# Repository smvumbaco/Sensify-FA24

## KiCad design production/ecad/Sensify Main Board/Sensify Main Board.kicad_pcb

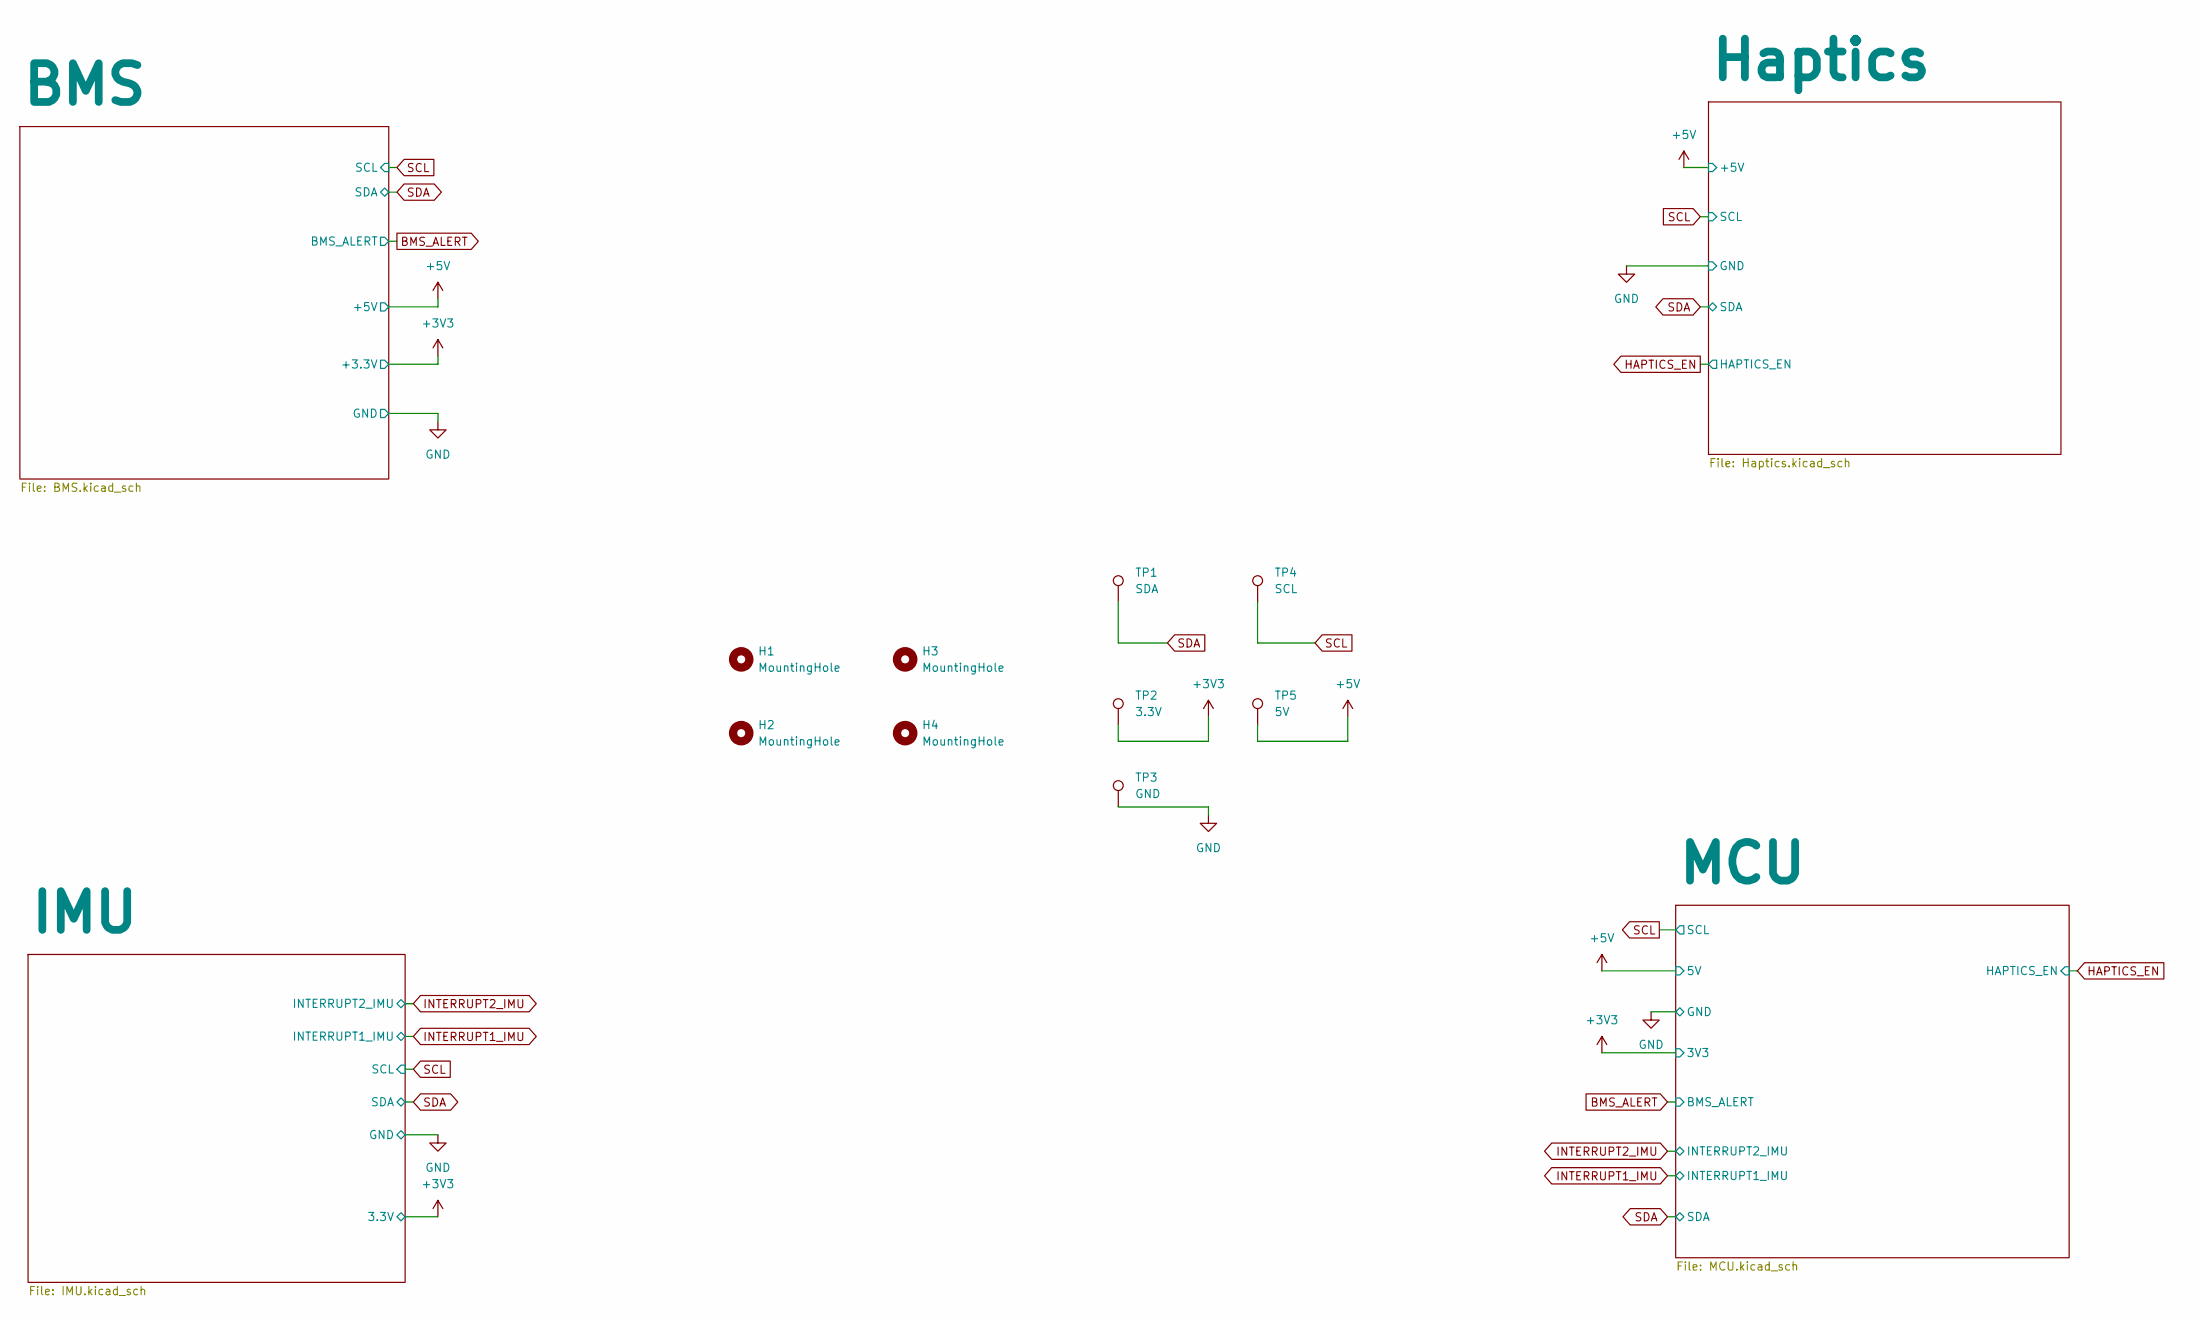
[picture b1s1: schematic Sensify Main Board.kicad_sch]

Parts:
H1, H2, H3, H4: MountingHole; MountingHole_3.2mm_M3
TP1: SDA; TestPoint_Pad_D2.0mm
TP2: 3.3V; TestPoint_Pad_D2.0mm
TP3: GND; TestPoint_Pad_D2.0mm
TP4: SCL; TestPoint_Pad_D2.0mm
TP5: 5V; TestPoint_Pad_D2.0mm

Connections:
+3V3: TP2.1; also elsewhere on the board
+5V: TP5.1; also elsewhere on the board
GND: TP3.1; also elsewhere on the board
SCL: TP4.1; also elsewhere on the board
SDA: TP1.1; also elsewhere on the board

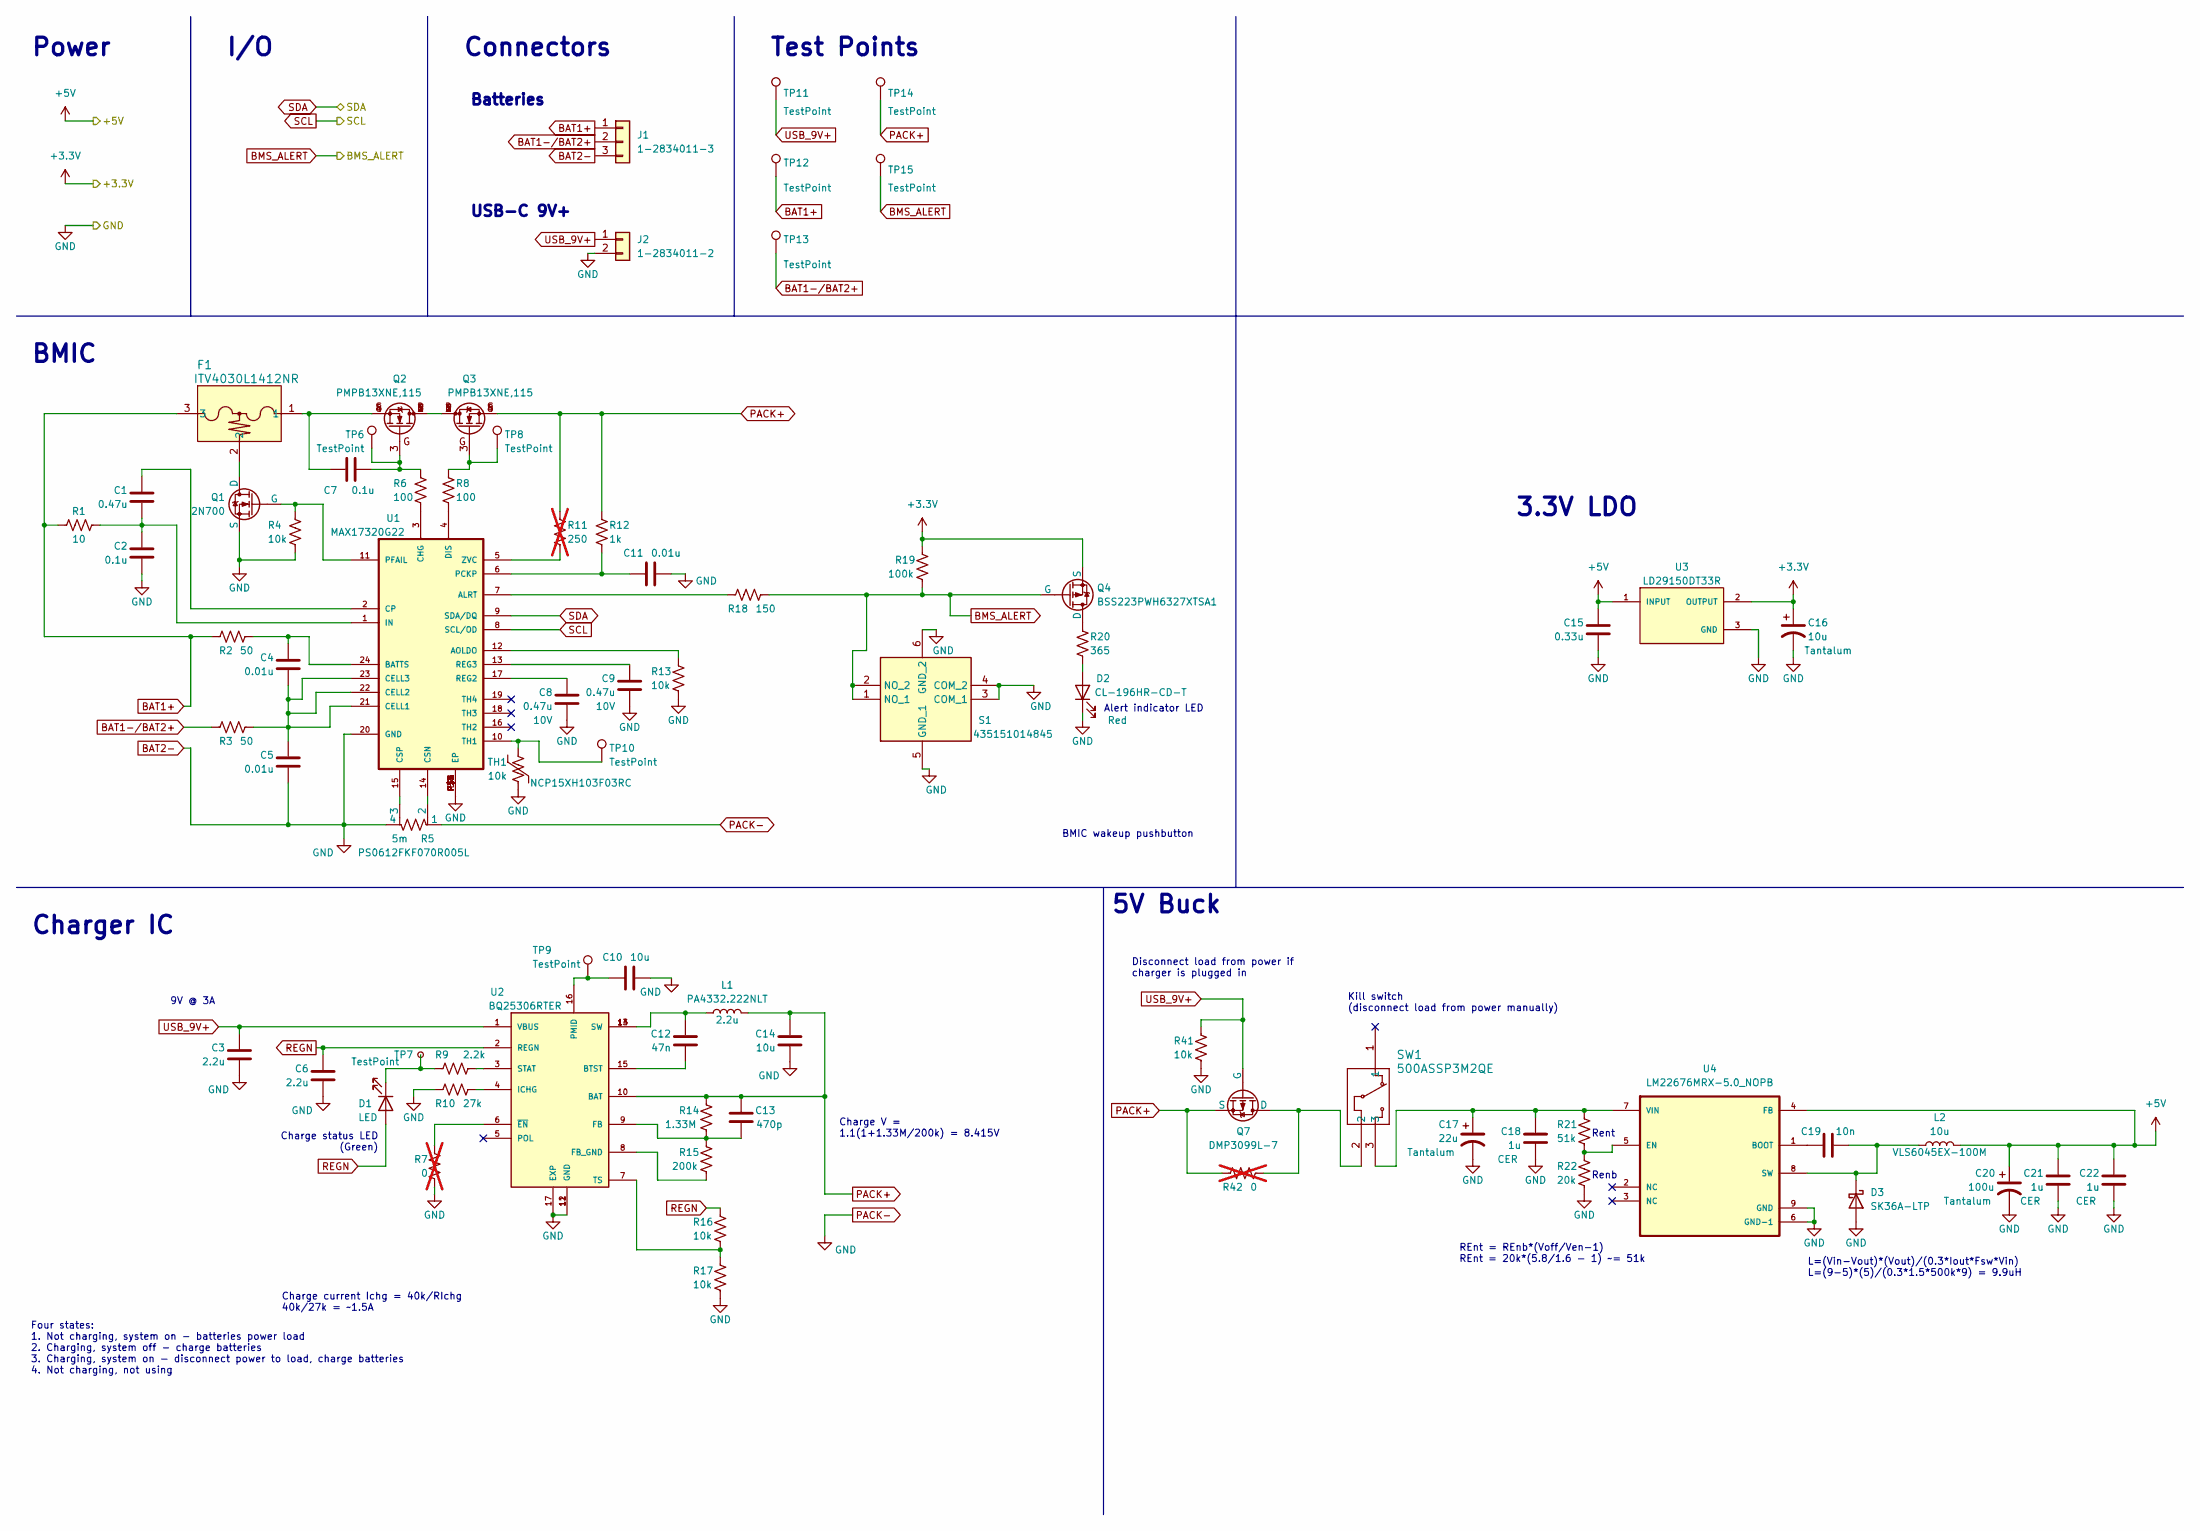
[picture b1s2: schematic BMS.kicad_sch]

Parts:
C1: 0.47u; C_0402_1005Metric_Pad0.74x0.62mm_HandSolder; LCSC C92361
C2, C7: 0.1u; C_0402_1005Metric_Pad0.74x0.62mm_HandSolder; LCSC C1581
C3: 2.2u; C_0603_1608Metric_Pad1.08x0.95mm_HandSolder; LCSC C43922
C4, C5, C11: 0.01u; C_0402_1005Metric_Pad0.74x0.62mm_HandSolder; LCSC C1524
C6: 2.2u; C_0402_1005Metric_Pad0.74x0.62mm_HandSolder; LCSC C72203
C8, C9: 0.47u; C_0402_1005Metric_Pad0.74x0.62mm_HandSolder; Voltage 10V; LCSC C92361
C10, C14: 10u; C_0805_2012Metric_Pad1.18x1.45mm_HandSolder; LCSC C15850
C12: 47n; C_0402_1005Metric_Pad0.74x0.62mm_HandSolder; LCSC C82219
C13: 470p; C_0402_1005Metric_Pad0.74x0.62mm_HandSolder; LCSC C26412
C15: 0.33u; C_0603_1608Metric_Pad1.08x0.95mm_HandSolder; Voltage 10V; LCSC C14790
C16: 10u; T491A; Part number T491A106K010AT; LCSC C15850
C17: 22u; CAPPM3528X210N; LCSC C110037
C18, C21, C22: 1u; C_0603_1608Metric_Pad1.08x0.95mm_HandSolder; LCSC C15849
C19: 10n; C_0603_1608Metric_Pad1.08x0.95mm_HandSolder; LCSC C7248
C20: 100u; CAPPM3528X210N; LCSC C1953001
D1: LED; D_0603_1608Metric_Pad1.05x0.95mm_HandSolder; Part number LTST-C190GKT; LCSC C125093
D2: CL-196HR-CD-T; D_0603_1608Metric_Pad1.05x0.95mm_HandSolder; LCSC C6150013
D3: SK36A-LTP; DIOM5225X244N; LCSC C106867
F1: ITV4030L1412NR; ITV4030_LTF; LCSC C3672263
J1: 1-2834011-3; 128340113
J2: 1-2834011-2; 128340112
L1: 2.2u; IND_PA4332.222NLT_PUL; part number PA4332.222NLT; LCSC C3222957
L2: 10u; IND_VLS6045EX-100M; part number VLS6045EX-100M; LCSC C360734
Q1: 2N700; SOT95P240X111-3N; LCSC C8545
Q2, Q3: PMPB13XNE,115; DFN2020MD-6_SOT1220_NEX; LCSC C553019
Q4: BSS223PWH6327XTSA1; SOT65P210X100-3N; LCSC C3278612
Q7: DMP3099L-7; DMP3099L-7_DIO; LCSC C155244
R1: 10; R_0805_2012Metric_Pad1.20x1.40mm_HandSolder; LCSC C103908
R2, R3: 50; R_0805_2012Metric_Pad1.20x1.40mm_HandSolder; LCSC C2828807
R4, R13, R16, R17: 10k; R_0402_1005Metric_Pad0.72x0.64mm_HandSolder; LCSC C881209
R5: 5m; PS0612_2-10mOHM_YAG; Part number PS0612FKF070R005L
R6, R8: 100; R_0402_1005Metric_Pad0.72x0.64mm_HandSolder; LCSC C102747
R7, R42: 0; R_0402_1005Metric_Pad0.72x0.64mm_HandSolder; LCSC C60485; not fitted
R9: 2.2k; R_0402_1005Metric_Pad0.72x0.64mm_HandSolder; LCSC C25933
R10: 27k; R_0402_1005Metric_Pad0.72x0.64mm_HandSolder; Part number ERA-2ARB273X; LCSC C11896
R11: 250; R_0402_1005Metric_Pad0.72x0.64mm_HandSolder; LCSC C114755; not fitted
R12: 1k; R_0402_1005Metric_Pad0.72x0.64mm_HandSolder; LCSC C226698
R14: 1.33M; R_0402_1005Metric_Pad0.72x0.64mm_HandSolder; LCSC C5713265
R15: 200k; R_0402_1005Metric_Pad0.72x0.64mm_HandSolder; LCSC C25764
R18: 150; R_0402_1005Metric_Pad0.72x0.64mm_HandSolder; LCSC C25143
R19: 100k; R_0402_1005Metric_Pad0.72x0.64mm_HandSolder; LCSC C102750
R20: 365; R_0402_1005Metric_Pad0.72x0.64mm_HandSolder; LCSC C227016
R21: 51k; R_0603_1608Metric_Pad0.98x0.95mm_HandSolder; LCSC C95329
R22: 20k; R_0603_1608Metric_Pad0.98x0.95mm_HandSolder; LCSC C125934
R41: 10k; R_0402_1005Metric; LCSC C881209
S1: 435151014845; Manufacturer_Part_Number 435151014845; Mouser Part Number 710-435151014845
SW1: 500ASSP3M2QE; 500ASSP3M2QE_EWI
TH1: 10k; R_0402_1005Metric_Pad0.72x0.64mm_HandSolder; Part number NCP15XH103F03RC; LCSC C77131
TP6, TP7, TP8, TP9, TP10, TP11, TP12, TP13, TP14, TP15: TestPoint; TestPoint_Pad_D1.5mm
U1: MAX17320G22; TQFN-24; LCSC C2914309
U2: BQ25306RTER; IC_BQ25306RTER; PARTREV A; LCSC C3682611
U3: LD29150DT33R; DPAK456P972X240-3N; PARTREV 20; LCSC C155674
U4: LM22676MRX-5.0_NOPB; VREG_LM5017MR_NOPB; LCSC C485622

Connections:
+3V3: C16.1, Q4.3 (S), R19.1, U3.2 (OUTPUT); also elsewhere on the board
+5V: C15.1, C20.1, C21.1, C22.1, L2.2, U3.1 (INPUT), U4.4 (FB); also elsewhere on the board
BAT1+: F1.3, J1.1, R1.1, R2.2, TP12.1
BAT1-/BAT2+: J1.2, R3.2, TP13.1
BMS_ALERT: Q4.2 (G), R18.1, R19.2, S1.1 (NO_1), S1.2 (NO_2), TP15.1; also elsewhere on the board
GND: C2.2, C3.2, C5.2, C6.2, C8.2, C9.2, C10.2, C11.2, C14.2, C15.2, C16.2, C17.2, C18.2, C20.2, C21.2, C22.2, D2.1 (K), D3.2, J1.3, J2.2, Q1.3 (S), R4.2, R5.1, R5.4, R7.2, R10.2, R13.2, R17.2, R22.2, R41.2, S1.3 (COM_1), S1.4 (COM_2), S1.5 (GND_1), S1.6 (GND_2), TH1.1, U1.20 (GND), U1.EP, U1.P$1 (EP), U1.P$2 (EP), U1.P$3 (EP), U1.P$4 (EP), U1.P$5 (EP), U2.11 (GND), U2.12 (GND), U2.17 (EXP), U3.3 (GND), U4.6 (GND-1), U4.9 (GND); also elsewhere on the board
unnamed: C7.1, F1.1, Q2.4 (S), Q2.8 (S)
unnamed: C12.1, L1.1, U2.13 (SW), U2.14 (SW)
unnamed: D1.1 (K), R9.2, TP7.1
unnamed: D2.2 (A), R20.2
unnamed: F1.2, Q1.1 (D)
unnamed: Q1.2 (G), R4.1, U1.11 (PFAIL)
unnamed: Q2.1 (D), Q2.2 (D), Q2.5 (D), Q2.6 (D), Q2.7 (D), Q3.1 (D), Q3.2 (D), Q3.5 (D), Q3.6 (D), Q3.7 (D)
unnamed: C7.2, Q2.3 (G), R6.1, TP6.1
unnamed: Q3.3 (G), R8.1, TP8.1
unnamed: Q4.1 (D), R20.1
unnamed: Q7.1 (D), R42.1, SW1.2
unnamed: R18.2, U1.7 (ALRT)
unnamed: R13.1, U1.12 (AOLDO)
unnamed: C4.1, R2.1, U1.24 (BATTS)
unnamed: C4.2, C5.1, R3.1, U1.21 (CELL1), U1.22 (CELL2), U1.23 (CELL3)
unnamed: R6.2, U1.3 (CHG)
unnamed: C1.1, U1.2 (CP)
unnamed: R5.2, U1.14 (CSN)
unnamed: R5.3, U1.15 (CSP)
unnamed: R8.2, U1.4 (DIS)
unnamed: C1.2, C2.1, R1.2, U1.1 (IN)
unnamed: C11.1, R12.2, U1.6 (PCKP)
unnamed: C8.1, U1.17 (REG2)
unnamed: C9.1, U1.13 (REG3)
unnamed: TH1.2, TP10.1, U1.10 (TH1)
unnamed: R11.2, U1.5 (ZVC)
unnamed: C12.2, U2.15 (BTST)
unnamed: C13.2, R14.2, R15.1, U2.9 (FB)
unnamed: R15.2, U2.8 (FB_GND)
unnamed: R10.1, U2.4 (ICHG)
unnamed: C10.1, TP9.1, U2.16 (PMID)
unnamed: R9.1, U2.3 (STAT)
unnamed: R16.2, R17.1, U2.7 (TS)
unnamed: R7.1, U2.6 (~EN)
unnamed: C19.1, U4.1 (BOOT)
unnamed: R21.2, R22.1, U4.5 (EN)
unnamed: C19.2, D3.1, L2.1, U4.8 (SW)
unnamed: C17.1, C18.1, R21.1, SW1.3, U4.7 (VIN)
PACK+: C13.1, C14.1, L1.2, Q3.4 (S), Q3.8 (S), Q7.3 (S), R11.1, R12.1, R14.1, R42.2, TP14.1, U2.10 (BAT)
REGN: C6.1, D1.2 (A), R16.1, U2.2 (REGN)
SCL: U1.8 (SCL/OD); also elsewhere on the board
SDA: U1.9 (SDA/DQ); also elsewhere on the board
USB_9V+: C3.1, J2.1, Q7.2 (G), R41.1, TP11.1, U2.1 (VBUS)

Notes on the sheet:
REnt = REnb*(Voff/Ven-1) REnt = 20k*(5.8/1.6 - 1) ~= 51k
USB-C 9V+
Rent
5V Buck
BMIC wakeup pushbutton
Test Points
I/O
Alert indicator LED
Connectors
Charge V = 1.1(1+1.33M/200k) = 8.415V
L=(Vin-Vout)*(Vout)/(0.3*Iout*Fsw*Vin) L=(9-5)*(5)/(0.3*1.5*500k*9) = 9.9uH
3.3V LDO
Charger IC
Kill switch (disconnect load from power manually)
Batteries
Four states: 1. Not charging, system on - batteries power load 2. Charging, system off - charge batteries 3. Charging, system on - disconnect power to load, charge batteries 4. Not charging, not using
BMIC
Disconnect load from power if charger is plugged in
9V @ 3A
Power
Charge current Ichg = 40k/RIchg 40k/27k = ~1.5A
Charge status LED (Green)
Renb

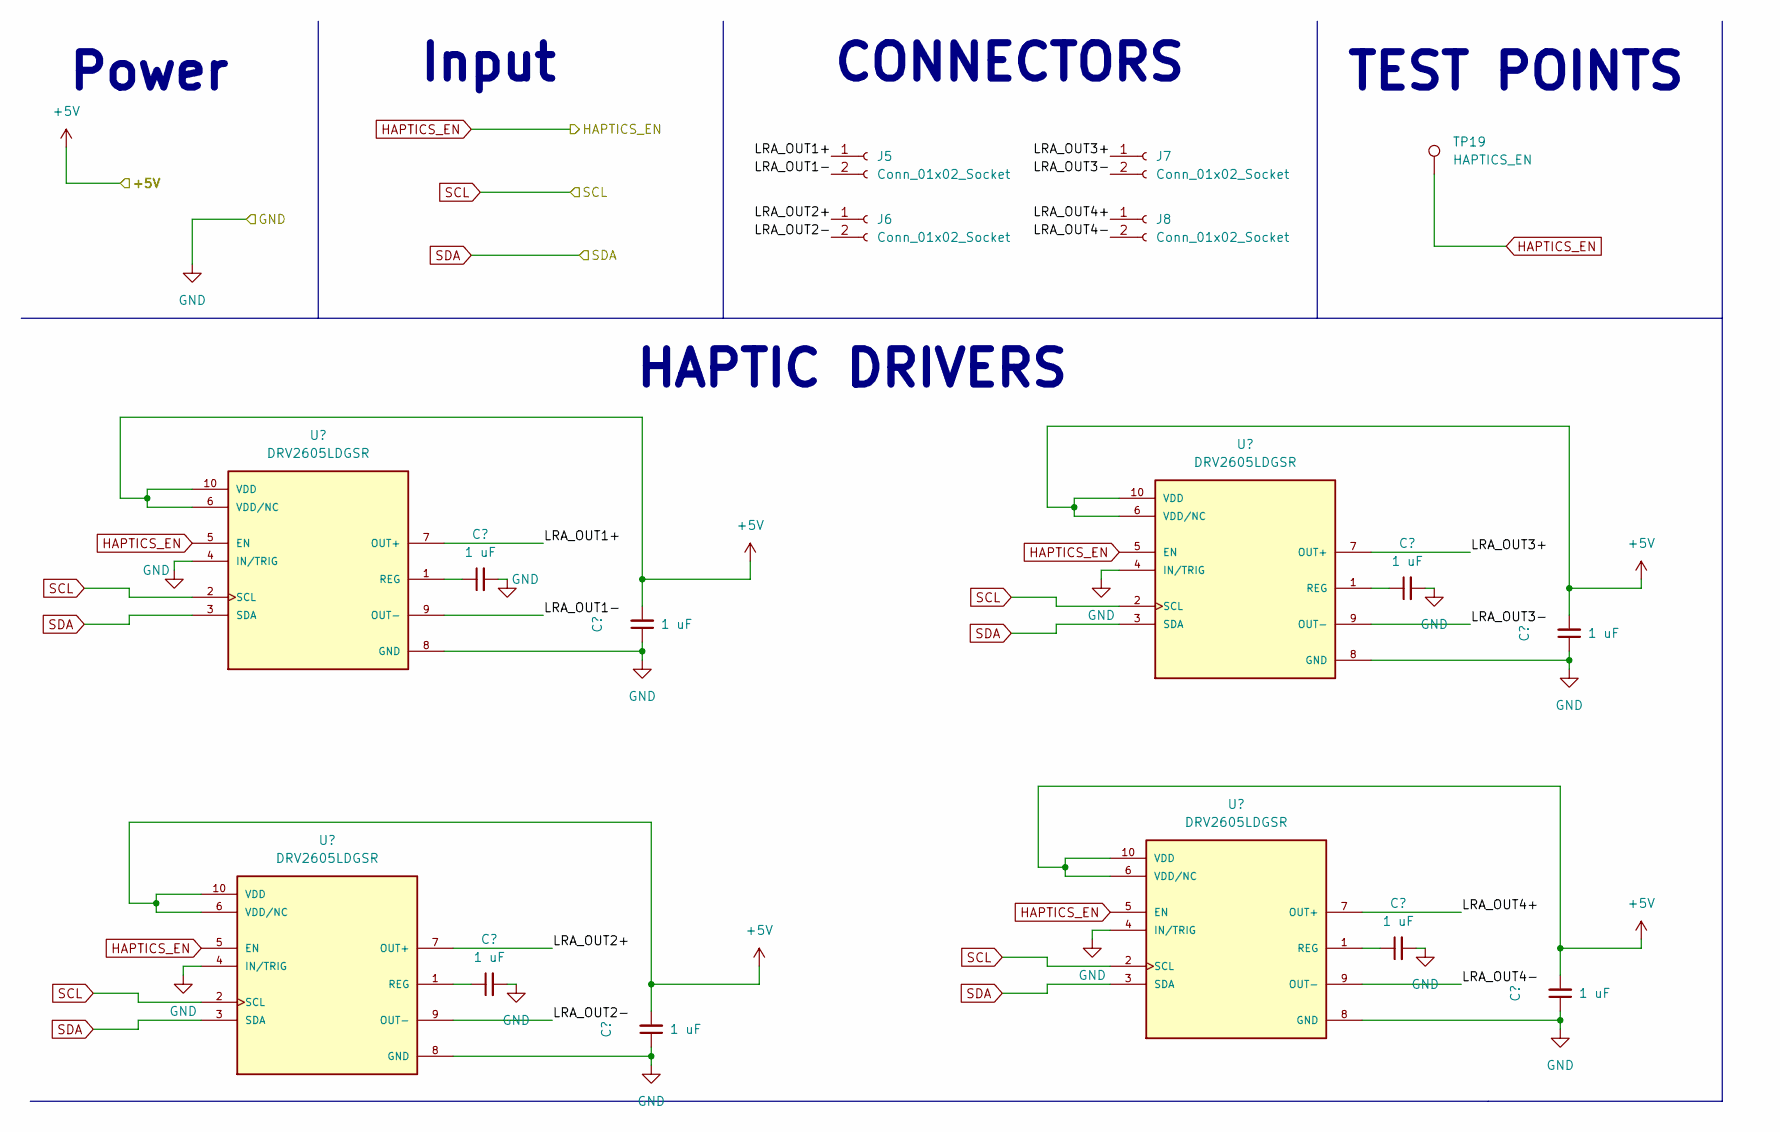
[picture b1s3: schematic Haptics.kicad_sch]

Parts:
C29, C30, C31, C32, C33, C34, C35, C36: 1 uF; C_0402_1005Metric; LCSC C87144
J5, J6, J7, J8: Conn_01x02_Socket; JST_EH_B2B-EH-A_1x02_P2.50mm_Vertical
TP19: HAPTICS_EN; TestPoint_Pad_D2.0mm
U7, U8, U9, U10: DRV2605LDGSR; SOP50P490X110-10N; PARTREV D; LCSC C527464

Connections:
+5V: C31.2, C32.2, C35.2, C36.2, U7.6 (VDD/NC), U7.10 (VDD), U8.6 (VDD/NC), U8.10 (VDD), U9.6 (VDD/NC), U9.10 (VDD), U10.6 (VDD/NC), U10.10 (VDD); also elsewhere on the board
/Haptics/LRA_OUT1+: J5.1, U7.7 (OUT+)
/Haptics/LRA_OUT1-: J5.2, U7.9 (OUT-)
/Haptics/LRA_OUT2+: J6.1, U8.7 (OUT+)
/Haptics/LRA_OUT2-: J6.2, U8.9 (OUT-)
/Haptics/LRA_OUT3+: J7.1, U10.7 (OUT+)
/Haptics/LRA_OUT3-: J7.2, U10.9 (OUT-)
/Haptics/LRA_OUT4+: J8.1, U9.7 (OUT+)
/Haptics/LRA_OUT4-: J8.2, U9.9 (OUT-)
GND: C29.2, C30.2, C31.1, C32.1, C33.2, C34.2, C35.1, C36.1, U7.4 (IN/TRIG), U7.8 (GND), U8.4 (IN/TRIG), U8.8 (GND), U9.4 (IN/TRIG), U9.8 (GND), U10.4 (IN/TRIG), U10.8 (GND); also elsewhere on the board
HAPTICS_EN: TP19.1, U7.5 (EN), U8.5 (EN), U9.5 (EN), U10.5 (EN); also elsewhere on the board
unnamed: C29.1, U7.1 (REG)
unnamed: C30.1, U8.1 (REG)
unnamed: C33.1, U9.1 (REG)
unnamed: C34.1, U10.1 (REG)
SCL: U7.2 (SCL), U8.2 (SCL), U9.2 (SCL), U10.2 (SCL); also elsewhere on the board
SDA: U7.3 (SDA), U8.3 (SDA), U9.3 (SDA), U10.3 (SDA); also elsewhere on the board

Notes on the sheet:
HAPTIC DRIVERS
CONNECTORS
Input
TEST POINTS
Power

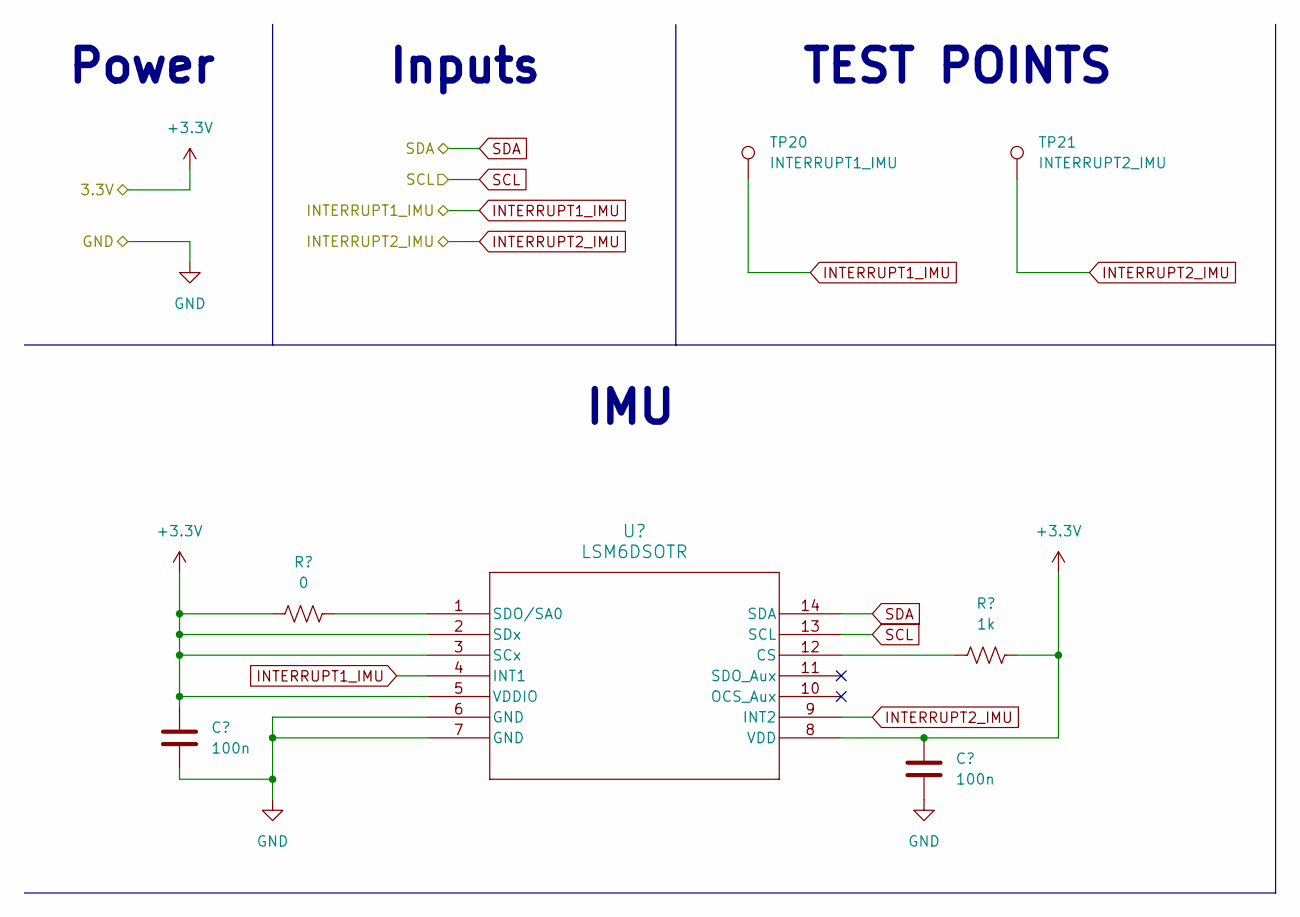
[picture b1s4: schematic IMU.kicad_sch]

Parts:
C37, C38: 100n; C_0402_1005Metric; LCSC C2180807
R39: 0; R_0402_1005Metric; LCSC C60485
R40: 1k; R_0402_1005Metric; LCSC C226698
TP20: INTERRUPT1_IMU; TestPoint_Pad_D2.0mm
TP21: INTERRUPT2_IMU; TestPoint_Pad_D2.0mm
U11: LSM6DSOTR; IMU_LSM6DSOTR; LCSC C2655100

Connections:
+3V3: C37.1, C38.1, R39.1, R40.2, U11.2 (SDx), U11.3 (SCx), U11.5 (VDDIO), U11.8 (VDD); also elsewhere on the board
GND: C37.2, C38.2, U11.6 (GND), U11.7 (GND); also elsewhere on the board
INTERRUPT1_IMU: TP20.1, U11.4 (INT1); also elsewhere on the board
INTERRUPT2_IMU: TP21.1, U11.9 (INT2); also elsewhere on the board
unnamed: R40.1, U11.12 (CS)
unnamed: R39.2, U11.1 (SDO/SA0)
SCL: U11.13 (SCL); also elsewhere on the board
SDA: U11.14 (SDA); also elsewhere on the board

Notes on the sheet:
IMU
Inputs
TEST POINTS
Power

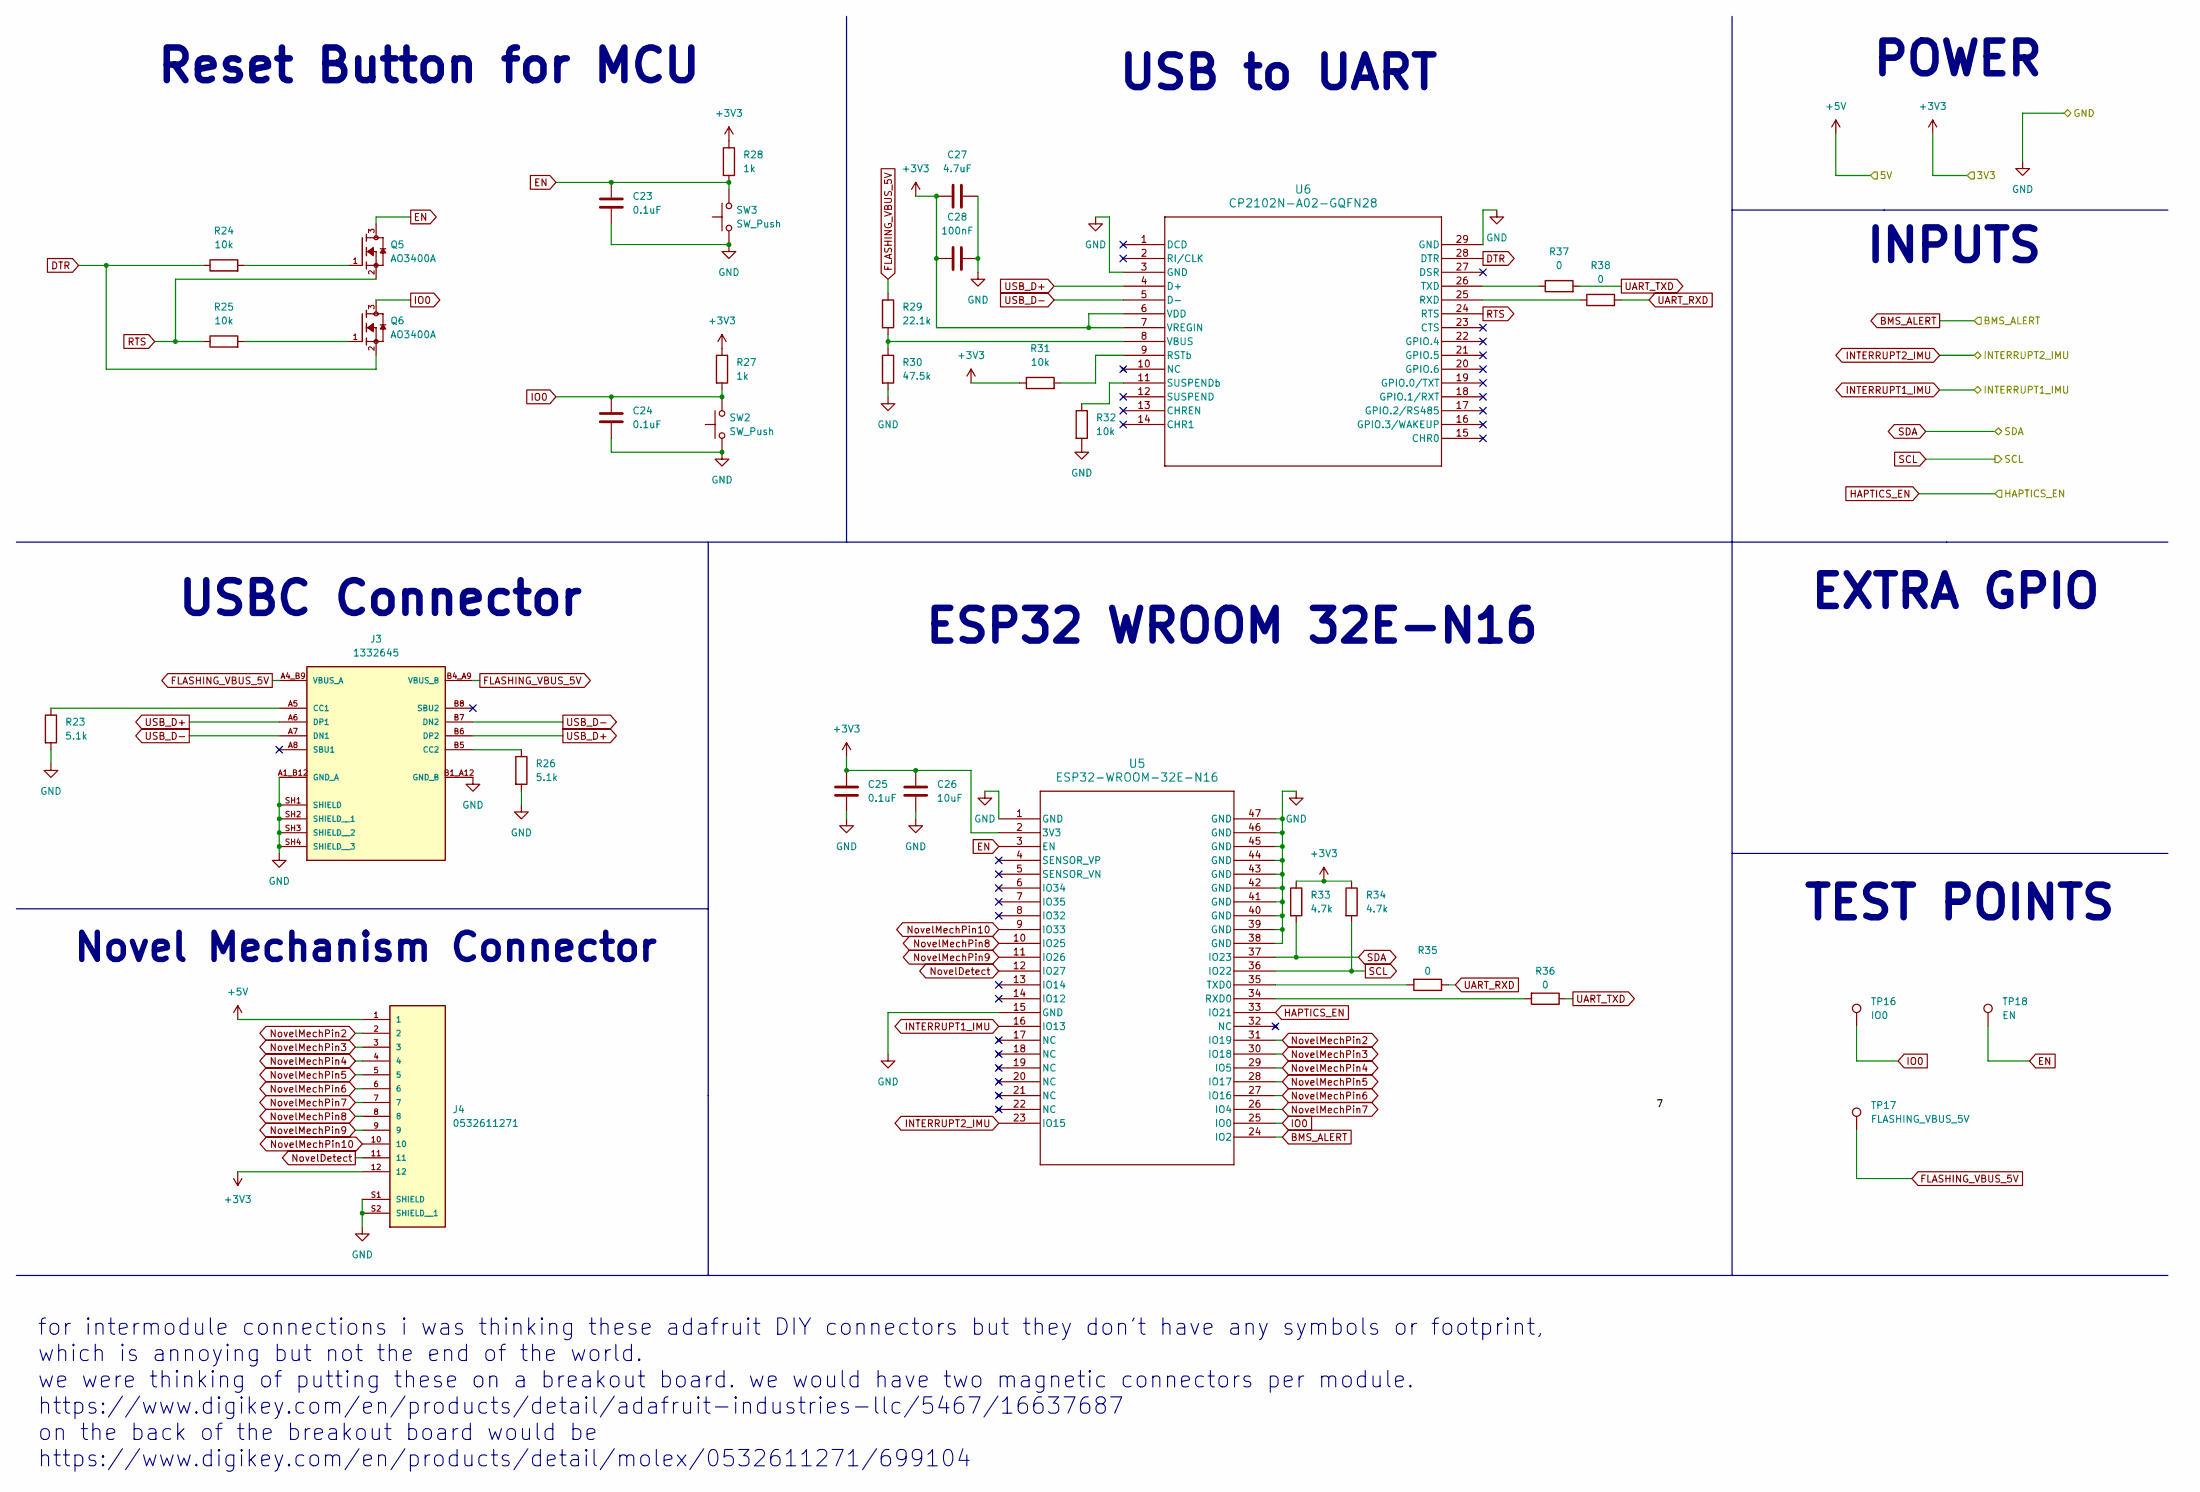
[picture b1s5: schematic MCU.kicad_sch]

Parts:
C23, C24, C25: 0.1uF; C_0402_1005Metric; LCSC C2180807
C26: 10uF; C_0402_1005Metric; LCSC C412251
C27: 4.7uF; C_0402_1005Metric; LCSC C5718966
C28: 100nF; C_0402_1005Metric; LCSC C2180807
J3: 1332645; PHOENIX_1332645; PARTREV 17.01.2022; LCSC C19193265
J4: 0532611271; MOLEX_0532611271; PARTREV J; LCSC C17393781
Q5, Q6: AO3400A; SOT95P280X125-3N; PARTREV L; LCSC C20917
R23, R26: 5.1k; R_0402_1005Metric; LCSC C105872
R24, R25, R31, R32: 10k; R_0402_1005Metric; LCSC C881209
R27, R28: 1k; R_0402_1005Metric; LCSC C226698
R29: 22.1k; R_0402_1005Metric; LCSC C163478
R30: 47.5k; R_0402_1005Metric; LCSC C137974
R33, R34: 4.7k; R_0402_1005Metric; LCSC C105870
R35, R36, R37, R38: 0; R_0402_1005Metric; LCSC C60485
SW2, SW3: SW_Push; SW_1825910-6-4
TP16: IO0; TestPoint_Pad_D2.0mm
TP17: FLASHING_VBUS_5V; TestPoint_Pad_D2.0mm
TP18: EN; TestPoint_Pad_D2.0mm
U5: ESP32-WROOM-32E-N16; ESP32-WROOM-32E_EXP; LCSC C701343
U6: CP2102N-A02-GQFN28; QFN28_5X5_SIL-M; LCSC C1550553

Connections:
+3V3: C25.1, C26.1, C27.1, C28.1, J4.12, R27.1, R28.1, R31.1, R33.1, R34.1, U5.2 (3V3), U6.6 (VDD), U6.7 (VREGIN); also elsewhere on the board
+5V: J4.1; also elsewhere on the board
BMS_ALERT: U5.24 (IO2); also elsewhere on the board
DTR: Q6.2, R24.1, U6.28 (DTR)
EN: C23.1, Q5.3, R28.2, SW3.2, TP18.1, U5.3 (EN)
FLASHING_VBUS_5V: J3.A4_B9 (VBUS_A), J3.B4_A9 (VBUS_B), R29.1, TP17.1
GND: C23.2, C24.2, C25.2, C26.2, C27.2, C28.2, J3.A1_B12 (GND_A), J3.B1_A12 (GND_B), J3.SH1 (SHIELD), J3.SH2 (SHIELD__1), J3.SH3 (SHIELD__2), J3.SH4 (SHIELD__3), J4.S1 (SHIELD), J4.S2 (SHIELD__1), R23.2, R26.2, R30.2, R32.2, SW2.1, SW3.1, U5.1 (GND), U5.15 (GND), U5.38 (GND), U5.39 (GND), U5.40 (GND), U5.41 (GND), U5.42 (GND), U5.43 (GND), U5.44 (GND), U5.45 (GND), U5.46 (GND), U5.47 (GND), U6.3 (GND), U6.29 (GND); also elsewhere on the board
HAPTICS_EN: U5.33 (IO21); also elsewhere on the board
INTERRUPT1_IMU: U5.16 (IO13); also elsewhere on the board
INTERRUPT2_IMU: U5.23 (IO15); also elsewhere on the board
IO0: C24.1, Q6.3, R27.2, SW2.2, TP16.1, U5.25 (IO0)
unnamed: J3.A5 (CC1), R23.1
unnamed: J3.B5 (CC2), R26.1
unnamed: Q5.1, R24.2
unnamed: Q6.1, R25.2
unnamed: R36.2, U5.34 (RXD0)
unnamed: R35.2, U5.35 (TXD0)
unnamed: R31.2, U6.9 (RSTb)
unnamed: R38.1, U6.25 (RXD)
unnamed: R32.1, U6.11 (SUSPENDb)
unnamed: R37.1, U6.26 (TXD)
unnamed: R29.2, R30.1, U6.8 (VBUS)
NovelDetect: J4.11, U5.12 (IO27)
NovelMechPin2: J4.2, U5.31 (IO19)
NovelMechPin3: J4.3, U5.30 (IO18)
NovelMechPin4: J4.4, U5.29 (IO5)
NovelMechPin5: J4.5, U5.28 (IO17)
NovelMechPin6: J4.6, U5.27 (IO16)
NovelMechPin7: J4.7, U5.26 (IO4)
NovelMechPin8: J4.8, U5.10 (IO25)
NovelMechPin9: J4.9, U5.11 (IO26)
NovelMechPin10: J4.10, U5.9 (IO33)
RTS: Q5.2, R25.1, U6.24 (RTS)
SCL: R34.2, U5.36 (IO22); also elsewhere on the board
SDA: R33.2, U5.37 (IO23); also elsewhere on the board
UART_RXD: R35.1, R38.2
UART_TXD: R36.1, R37.2
USB_D+: J3.A6 (DP1), J3.B6 (DP2), U6.4 (D+)
USB_D-: J3.A7 (DN1), J3.B7 (DN2), U6.5 (D-)

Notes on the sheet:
Novel Mechanism Connector
POWER
USBC Connector
ESP32 WROOM 32E-N16
for intermodule connections i was thinking these adafruit DIY connectors but they don't have any symbols or footprint, which is annoying but not the end of the world. we were thinking of putting these on a breakout board. we would have two magnetic connectors per module. https://www.digikey.com/en/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
Reset Button for MCU
EXTRA GPIO
USB to UART
INPUTS
TEST POINTS

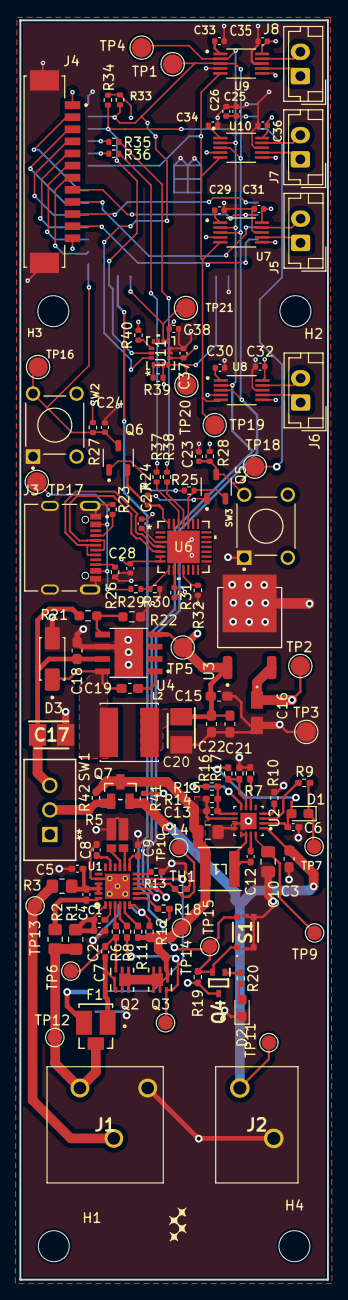
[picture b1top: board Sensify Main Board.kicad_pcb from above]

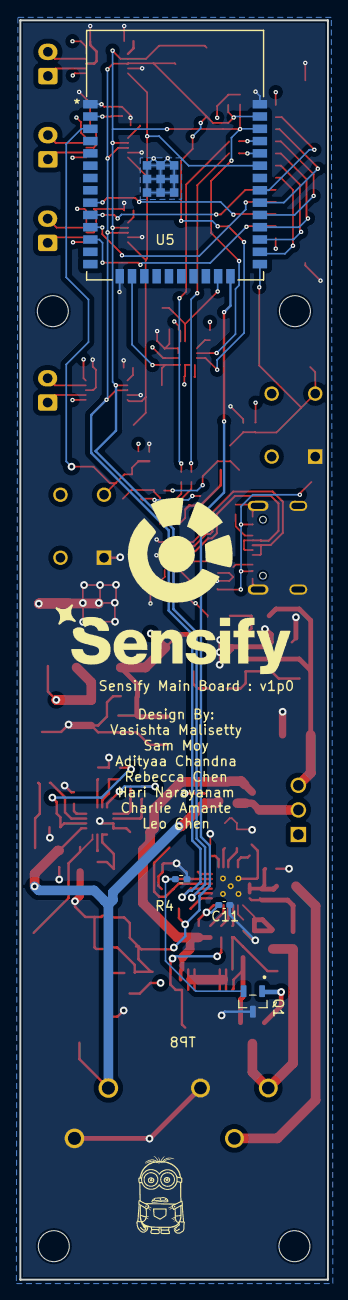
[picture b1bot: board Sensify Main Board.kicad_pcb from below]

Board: 4 copper layers, 31.8 x 130.0 mm, 142 parts (4 on the bottom side), 96 nets.
